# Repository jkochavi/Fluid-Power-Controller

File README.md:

# Fluid-Power-Controller
This software requires the use of STM32FreeRTOS.

The following files and libraries were created by other groups. 

Please download the following libraries/source files into the source code for this project:
- PrintStream.h
- STM32FreeRTOS.h
- "Easy Nextion Library" by Seithan
    - https://github.com/Seithan/EasyNextionLibrary.git
- "arduino-mcp2515" library by autowp
    - https://github.com/autowp/arduino-mcp2515.git
- ME 507 support files by spluttflob
    - All files necessary for inter-task variable sharing in FreeRTOS

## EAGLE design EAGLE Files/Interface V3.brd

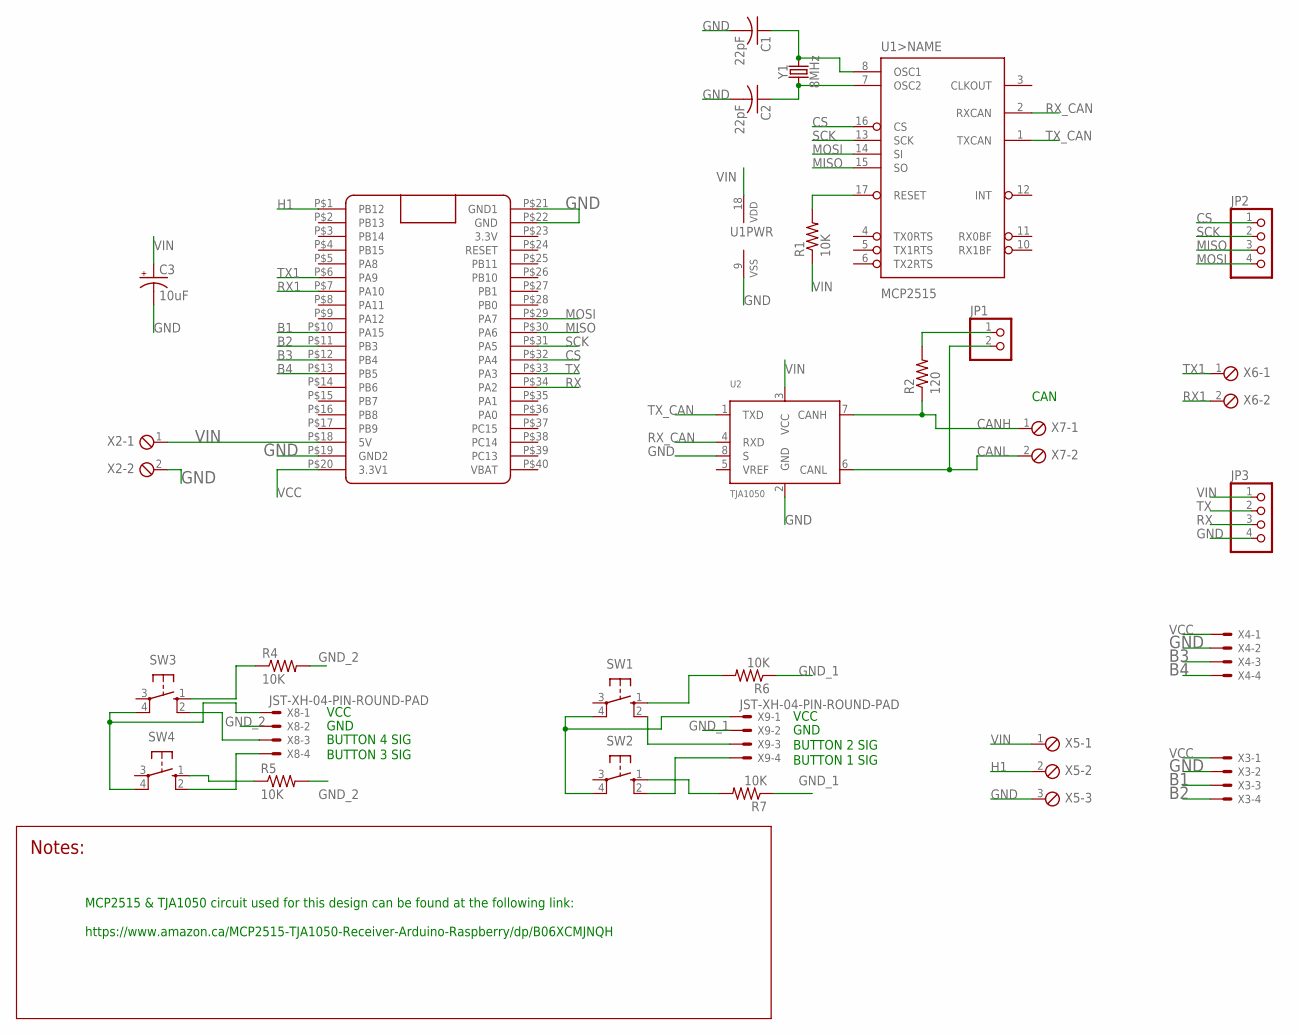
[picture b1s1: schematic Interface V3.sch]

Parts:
C1, C2: 22pF; C0805
C3: 10uF; CT3216
JP1: PINHD-1X2; 1X02
JP2, JP3: PINHD-1X4; 1X04
R1, R4, R5, R6, R7: 10K; R0805
R2: 120; R0805
SW1, SW2, SW3, SW4: PUSHBUTTON; B3F-10XX
U1: MCP2515; SO18W
U2: TJA1050; SOT96-1
U$1: BLUE_PILL
X2, X6, X7: SCREWTERM_2P_381; 2POL381
X3, X4: JST-XH-04-PIN-LONG-PAD; JST-XH-04-PACKAGE-LONG-PAD
X5: SCREWTERM_3P_381; 3POL381
X8, X9: JST-XH-04-PIN-ROUND-PAD; JST-XH-04-PACKAGE-ROUND-PAD
Y1: 8MHz; HC49US

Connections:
B1: U$1.P$10 (PA15), X3.3
B2: U$1.P$11 (PB3), X3.4
B3: U$1.P$12 (PB4), X4.3
B4: U$1.P$13 (PB5), X4.4
CANH: R2.1, U2.7 (CANH), X7.1
CANL: JP1.2, U2.6 (CANL), X7.2
CS: JP2.1, U1.16 (CS), U$1.P$32 (PA4)
GND: C1.2, C2.2, C3.-, JP3.4, U1.9 (VSS), U2.2 (GND), U2.8 (S), U$1.P$19 (GND2), U$1.P$21 (GND1), U$1.P$22 (GND), X2.2, X3.2, X4.2, X5.3
GND_1: R6.1, R7.1, X9.2
GND_2: R4.2, R5.2, X8.2
H1: U$1.P$1 (PB12), X5.2
MISO: JP2.3, U1.15 (SO), U$1.P$30 (PA6)
MOSI: JP2.4, U1.14 (SI), U$1.P$29 (PA7)
unnamed: C2.1, U1.7 (OSC2), Y1.1
unnamed: C1.1, U1.8 (OSC1), Y1.2
unnamed: R1.2, U1.17 (RESET)
unnamed: SW3.2 (S1), X8.3
unnamed: JP1.1, R2.2
unnamed: SW4.2 (S1), X8.4
unnamed: R4.1, SW3.1 (S)
unnamed: R5.1, SW4.1 (S)
unnamed: SW3.4 (P1), SW4.4 (P1), X8.1
unnamed: R6.2, SW1.1 (S)
unnamed: R7.2, SW2.1 (S)
unnamed: SW1.2 (S1), X9.3
unnamed: SW2.2 (S1), X9.4
unnamed: SW1.4 (P1), SW2.4 (P1), X9.1
RX: JP3.3, U$1.P$34 (PA2)
RX1: U$1.P$7 (PA10), X6.2
RX_CAN: U1.2 (RXCAN), U2.4 (RXD)
SCK: JP2.2, U1.13 (SCK), U$1.P$31 (PA5)
TX: JP3.2, U$1.P$33 (PA3)
TX1: U$1.P$6 (PA9), X6.1
TX_CAN: U1.1 (TXCAN), U2.1 (TXD)
VCC: U$1.P$20 (3.3V1), X3.1, X4.1
VIN: C3.+, JP3.1, R1.1, U1.18 (VDD), U2.3 (VCC), U$1.P$18 (5V), X2.1, X5.1

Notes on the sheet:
VCC
GND
BUTTON 4 SIG
BUTTON 3 SIG
BUTTON 2 SIG
BUTTON 1 SIG
CAN
MCP2515 & TJA1050 circuit used for this design can be found at the following link: https://www.amazon.ca/MCP2515-TJA1050-Receiver-Arduino-Raspberry/dp/B06XCMJNQH

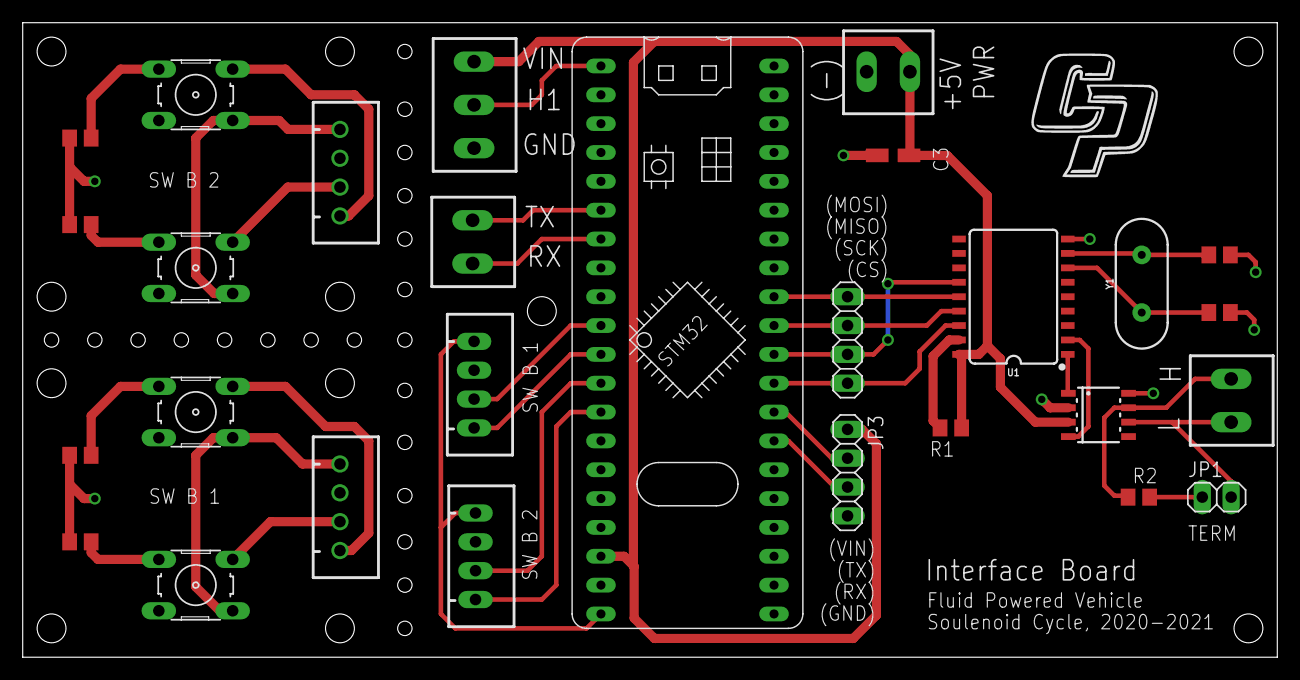
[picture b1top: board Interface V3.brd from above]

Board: 2 copper layers, 110.5 x 55.9 mm, 28 parts (0 on the bottom side), 36 nets.

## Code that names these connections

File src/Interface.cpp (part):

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#include "SPI.h"                 // Include SPI library
#include "mcp2515.h"             // Include MCP2515 library
/// @brief Macro definition for GPIO pin attached to coast button.
#define coastButton  PA15        // GPIO pin for coast mode button
/// @brief Macro definition for GPIO pin attached to direct drive button.
#define directButton PB3         // GPIO pin for direct drive button
/// @brief Macro definition for GPIO pin attached to boost mode button
#define boostButton  PB4         // GPIO pin for boost mode button
/// @brief Macro definition for GPIO pin attached to regenerative braking button.
#define regenButton  PB5         // GPIO pin for regen mode button
/// @brief Macro definition for GPIO pin attached to hall effect sensor
#define HALL1        PB12        // GPIO pin for hall effect sensor
/// @brief Macro definition for GPIO pin atached to the MCP2515 chip select
#define CS           PA4         // Chip select pin for MCP2515

/** @brief This variable keeps track of which drive mode the vehicle is in. 
 *         This value is when a button is pressed. 
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    // It will be used to run the task at precise intervals
    TickType_t xLastWakeTime = xTaskGetTickCount();
    // A UART serial object used to communicate with the display.
    HardwareSerial NEXSerial(PA3, PA2);                                      // Create serial port at desired GPIO pins
    NEXSerial.begin(9600);                                                   // Init the serial port at 9600 baud
    // A Nextion class object used to communicate with the display.
    EasyNex myNextion(NEXSerial);                                            // Create a Nextion object
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
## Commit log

2021-01-07 Initial commit after work on software.
2021-01-07 Recent changes.
2021-02-16 Altered CAN message ID
2021-02-23 Added Doxygen documentation.
2021-02-23 Fixed file locations.
2021-02-23 Added documentation.
2021-02-23 Added image-hosting files.
2021-02-24 Support image changes.
2021-02-24 Updated documentation.
2021-02-24 Updated documentatin
2021-02-27 Modified CAN tasks.
2021-03-02 Modified documentation.
2021-03-05 Added PLC readout support picture.
2021-03-05 Added Matlab screenshot.
2021-03-05 Added CAN page.
2021-03-08 Added HF Impulse Screenshots
2021-03-08 Added HF Impulse Screenshots.
2021-03-08 Modified documentation for HF Impulse.
2021-03-08 Modified image size.
2021-03-08 Modified button assignments.
2021-03-10 Fixed typo.
2021-03-10 Updated date.
2021-03-13 Modified to match new Nextion program.
2021-03-19 Added new screen capture of HF Impulse file.
2021-03-22 Added CAN status boolean.
2021-03-22 Implement CAN status boolean for display.
2021-03-24 Updated documentation and work on speed calculations.
2021-03-24 Updated Doxygen configuration.
2021-03-24 Updated task stack sizes and timing.
2021-03-24 Fixing task diagram.
2021-03-24 Added EAGLE files.
2021-03-24 Added new pages for EAGLE files.
2021-03-24 Added links to STL files.
2021-03-25 Implemented FSM for hall effect sensor. Fixed calculations.
2021-03-25 Updated documentation for hall effect task.
2021-03-25 Cleaned up files.
2021-03-25 Added new interface screenshots.
2021-03-25 Updated documentation with new interface screenshots.
2021-03-25 Updated renders with new interface.
2021-03-26 Added new picture.
2021-03-26 Added new image.
2021-03-26 Updated Nextion documentation page.
2021-03-29 Added embedded video to mainpage!
2021-03-30 Added pictures from button module water testing.
2021-03-30 Added design verification documentation.
2021-03-31 Modified CAN reception for 16-bit data.
2021-03-31 Added 16-bit transmission screenshots.
2021-03-31 Modified HF Impulse documentation.
2021-04-01 Added function to convert raw sensor reading into psi.
2021-04-03 Fixed bug that prevented drive mode reception from Nextion.
2021-04-03 Modified documentation
2021-04-03 Fixed pressure transducer calibration.
2021-04-04 Fixed pressure calculation.
2021-04-04 Added pressure transducer calibration curve.
2021-04-04 Linked to embedded video.
2021-04-05 Added new HF Impulse screenshot.
2021-04-05 Updated HF Impulse page with new program screenshot.
2021-04-05 Got rid of pressure calculation offset.
2021-04-07 Added STL file for screen stand.
2021-04-08 Fixed pressure calculation to calibrated curve fit.
2021-04-08 Added calibration plot.
2021-04-08 Added screenshot of setBitrate().
2021-04-08 Fixed typos.
2021-04-12 Added HF Impulse & Nextion files.
2021-04-12 Added links to HF Impulse and Nextion files.
2021-04-12 Added more final pictures.
2021-04-12 Switching out for better quality picture.
2021-04-12 Switching
2021-04-12 Switching to add logo to picture.
2021-04-12 Deleted unused picture, added to mainpage.
2021-04-12 Updated documentation
2021-04-12 Added screen stand image.
2021-04-13 Added section on screen stand.

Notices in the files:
parts and their libraries:
EDITED_SparkFun_IC_Comms: Licensing: Creative Commons ShareAlike 4.0 International - https://creativecommons.org/licenses/by-sa/4.0
